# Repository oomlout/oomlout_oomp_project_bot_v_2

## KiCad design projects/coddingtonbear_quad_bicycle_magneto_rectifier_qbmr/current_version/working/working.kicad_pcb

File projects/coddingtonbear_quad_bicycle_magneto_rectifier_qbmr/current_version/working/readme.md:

# quad_bicycle_magneto_rectifier
 
## summary 
* id: coddingtonbear_quad_bicycle_magneto_rectifier_qbmr
* user: coddingtonbear
* name: quad_bicycle_magneto_rectifier
* board: qbmr
* repo: https://github.com/coddingtonbear/quad-bicycle-magneto-rectifier
* src_file_repo_kicad_pcb: hardware/qbmr.kicad_pcb
* src_file_repo_kicad_pcb_link: https://github.com/coddingtonbear/quad-bicycle-magneto-rectifier/tree/master/hardware/qbmr.kicad_pcb

* src_file_repo_sch: hardware/qbmr.sch
* src_file_repo_sch_link: https://github.com/coddingtonbear/quad-bicycle-magneto-rectifier/tree/master/hardware/qbmr.sch
* full details link: https://github.com/oomlout/oomlout_oomp_project_bot_v_2/tree/main/projects/coddingtonbear_quad_bicycle_magneto_rectifier_qbmr/current_version/working

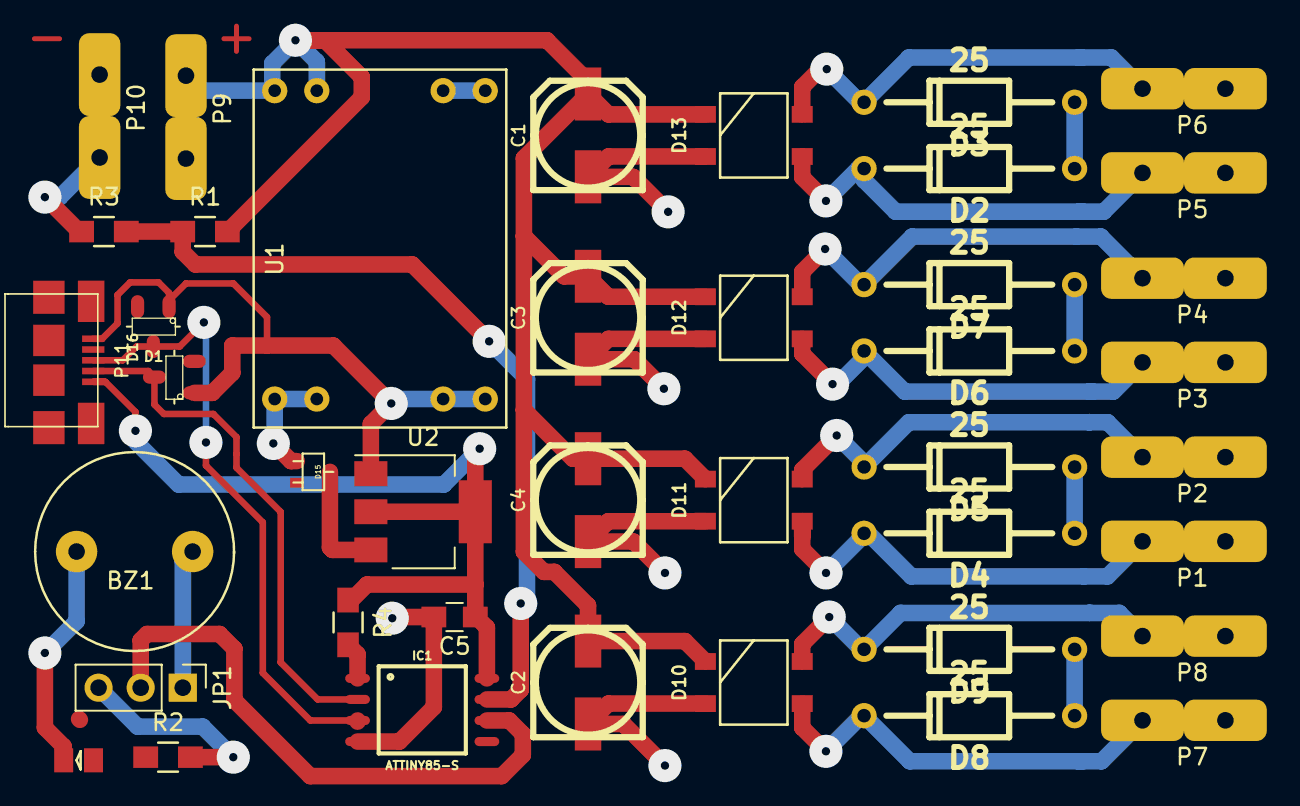
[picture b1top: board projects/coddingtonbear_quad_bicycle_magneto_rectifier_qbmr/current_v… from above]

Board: 2 copper layers, 41 parts (0 on the bottom side), 25 nets.

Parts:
BZ1: Buzzer; 12mm_buzzer
C1, C2, C3, C4: ?; SMD_PANASONIC_D
C5: 0.1u; C_0805_HandSoldering
D1, D16: 3.6; DIODE-SOT-23-3
D2, D3, D4, D5, D6, D7, D8, D9: 25; DO204AL_500
D10, D11, D12, D13: MB24S(+); SM-TO-269AA
D14: LED; 0805-LED
D15: D; SOT323_diode
IC1: ATTINY85-S; SOIC8
JP1: Jumper_NC_Dual; Pin_Header_Straight_1x03_Pitch2.54mm
P1, P2, P3, P4, P5, P6, P7, P8: CONN_01X01; TAB
P9: VCC; TAB
P10: GND; TAB
P11: USB_OTG; MICRO-B_USB-INVERTED
R1: 1k; R_0805_HandSoldering
R2: 500; R_0805_HandSoldering
R3: 200; R_0805_HandSoldering
R4: 10k; R_0805_HandSoldering
U1: MP1584EN
U2: AP111750; SOT-223

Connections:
GND: BZ1.2, C1.2, C2.2, C3.2, C4.2, C5.2, D1.2, D10.2, D11.2, D12.2, D13.2, D14.1, D16.2, IC1.4, P10.1, P11.5, R3.1, U1.1, U1.3, U2.1
unnamed: BZ1.1, JP1.1
unnamed: D2.2, D3.2
unnamed: D4.2, D5.2
unnamed: D6.2, D7.2
unnamed: D8.2, D9.2
unnamed: D8.1, D10.3, P7.1
unnamed: D9.1, D10.4, P8.1
unnamed: D4.1, D11.3, P1.1
unnamed: D5.1, D11.4, P2.1
unnamed: D6.1, D12.3, P3.1
unnamed: D7.1, D12.4, P4.1
unnamed: D2.1, D13.3, P5.1
unnamed: D3.1, D13.4, P6.1
unnamed: D14.2, R2.1
unnamed: D15.1, U2.3
unnamed: D15.2, U1.4
unnamed: IC1.1, R4.2
unnamed: IC1.6, JP1.2
unnamed: IC1.7, R1.1, R3.2
unnamed: JP1.3, R2.2
USBD+: D16.1, IC1.3, P11.3
USBD-: D1.1, IC1.2, P11.2
VCC: C1.1, C2.1, C3.1, C4.1, D10.1, D11.1, D12.1, D13.1, P9.1, R1.2, U1.2
VUSB: C5.1, IC1.8, P11.1, R4.1, U2.2, U2.4

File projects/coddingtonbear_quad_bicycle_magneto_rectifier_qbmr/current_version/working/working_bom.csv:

"Id";"Designator";"Footprint";"Quantity";"Designation";"Supplier and ref";
1;"P10";"TAB";1;"GND";;;
2;"P9";"TAB";1;"VCC";;;
3;"P8,P7,P6,P5,P4,P1,P2,P3";"TAB";8;"CONN_01X01";;;
4;"D12,D10,D11,D13";"SM-TO-269AA";4;"MB24S(+)";;;
5;"C4,C3,C2,C1";"SMD_PANASONIC_D";4;"?";;;
6;"R1";"R_0805_HandSoldering";1;"1k";;;
7;"R2";"R_0805_HandSoldering";1;"500";;;
8;"D14";"0805-LED";1;"LED";;;
9;"BZ1";"12mm_buzzer";1;"Buzzer";;;
10;"D15";"SOT323_diode";1;"D";;;
11;"U1";"MP1584EN";1;"MP1584EN";;;
12;"P11";"MICRO-B_USB-INVERTED";1;"USB_OTG";;;
13;"IC1";"SOIC8";1;"ATTINY85-S";;;
14;"R3";"R_0805_HandSoldering";1;"200";;;
15;"U2";"SOT-223";1;"AP111750";;;
16;"C5";"C_0805_HandSoldering";1;"0.1u";;;
17;"D1,D16";"DIODE-SOT-23-3";2;"3.6";;;
18;"JP1";"Pin_Header_Straight_1x03_Pitch2.54mm";1;"Jumper_NC_Dual";;;
19;"D2,D3,D4,D5,D6,D7,D8,D9";"DO204AL_500";8;"25";;;
20;"R4";"R_0805_HandSoldering";1;"10k";;;

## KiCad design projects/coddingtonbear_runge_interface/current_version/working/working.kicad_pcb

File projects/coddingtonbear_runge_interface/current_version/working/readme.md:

# runge
 
## summary 
* id: coddingtonbear_runge_interface
* user: coddingtonbear
* name: runge
* board: interface
* repo: https://github.com/coddingtonbear/runge
* src_file_repo_kicad_pcb: hardware/interface/interface.kicad_pcb
* src_file_repo_kicad_pcb_link: https://github.com/coddingtonbear/runge/tree/master/hardware/interface/interface.kicad_pcb

* src_file_repo_sch: hardware/interface/interface.sch
* src_file_repo_sch_link: https://github.com/coddingtonbear/runge/tree/master/hardware/interface/interface.sch
* full details link: https://github.com/oomlout/oomlout_oomp_project_bot_v_2/tree/main/projects/coddingtonbear_runge_interface/current_version/working

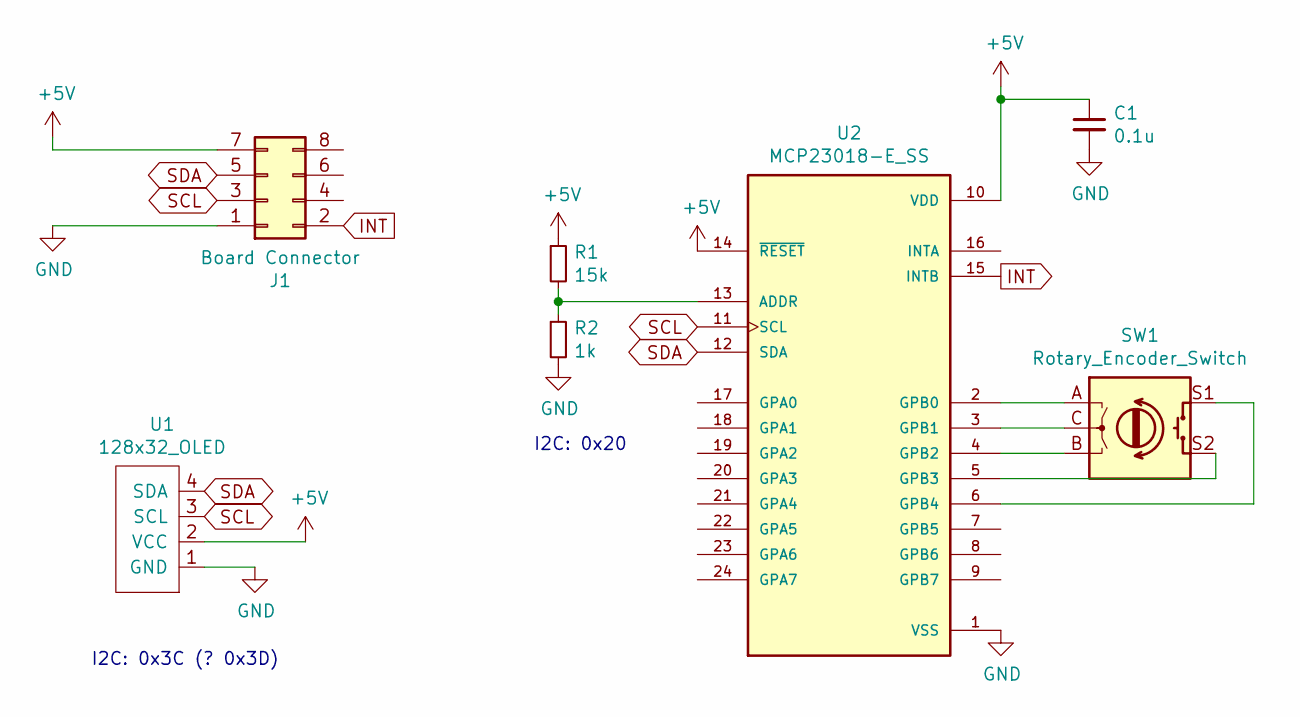
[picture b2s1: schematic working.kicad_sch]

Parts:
C1: 0.1u; 0805_Milling
J1: Board Connector; IDC-Header_2x04_P2.54mm_Vertical
R1: 15k; 0805_Milling
R2: 1k; 0805_Milling
SW1: Rotary_Encoder_Switch; RotaryEncoder_Alps_EC12E-Switch_Vertical_H20mm
U1: 128x32_OLED
U2: MCP23018-E_SS; SSOP-24_5.3x8.2mm_P0.65mm; PARTREV N/A

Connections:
+5V: C1.1, J1.7, R1.1, U1.2 (VCC), U2.10 (VDD), U2.14 (~RESET)
GND: C1.2, J1.1, R2.2, U1.1 (GND), U2.1 (VSS)
INT: J1.2, U2.15 (INTB)
unnamed: R1.2, R2.1, U2.13 (ADDR)
unnamed: SW1.A, U2.2 (GPB0)
unnamed: SW1.B, U2.4 (GPB2)
unnamed: SW1.C, U2.3 (GPB1)
unnamed: SW1.S1, U2.6 (GPB4)
unnamed: SW1.S2, U2.5 (GPB3)
SCL: J1.3, U1.3 (SCL), U2.11 (SCL)
SDA: J1.5, U1.4 (SDA), U2.12 (SDA)

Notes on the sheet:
I2C: 0x20
I2C: 0x3C (? 0x3D)

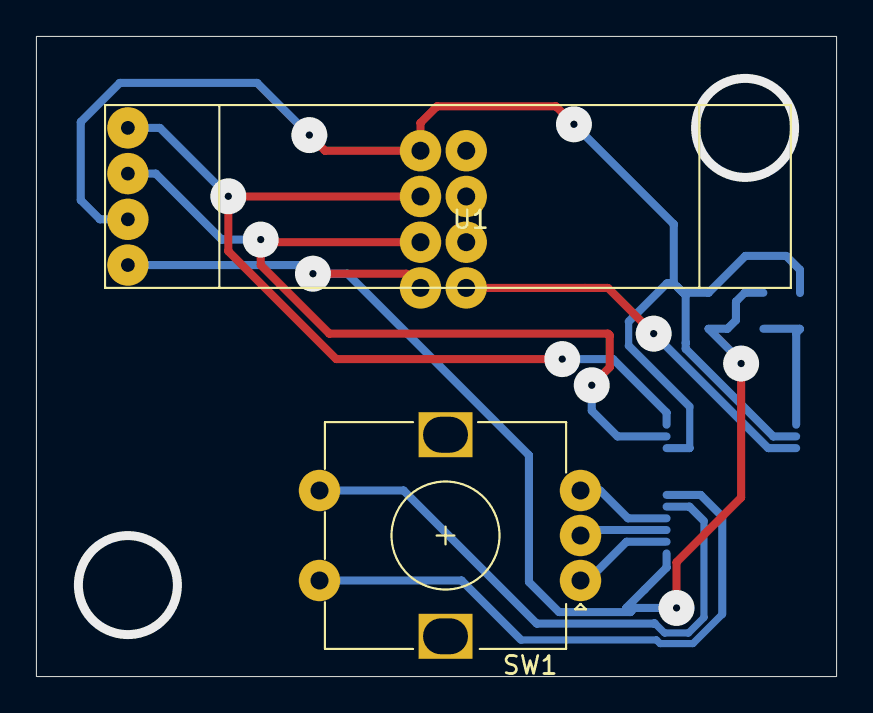
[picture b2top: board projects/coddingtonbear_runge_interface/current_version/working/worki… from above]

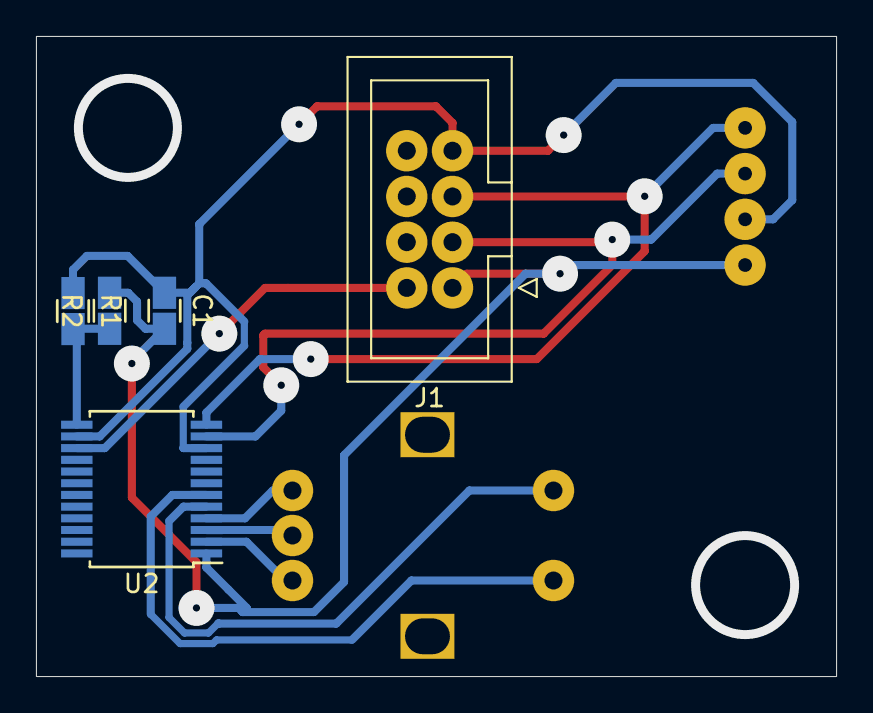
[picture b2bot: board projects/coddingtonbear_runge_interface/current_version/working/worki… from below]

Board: 2 copper layers, 44.4 x 35.6 mm, 7 parts (5 on the bottom side), 11 nets.

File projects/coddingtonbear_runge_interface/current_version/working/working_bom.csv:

"Id";"Designator";"Footprint";"Quantity";"Designation";"Supplier and ref";
1;"U1";"128x32_OLED";1;"128x32_OLED";;;
2;"SW1";"RotaryEncoder_Alps_EC12E-Switch_Vertical_H20mm";1;"Rotary_Encoder_Switch";;;
3;"C1";"0805_Milling";1;"0.1u";;;
4;"R1";"0805_Milling";1;"15k";;;
5;"R2";"0805_Milling";1;"1k";;;
6;"U2";"SSOP-24_5.3x8.2mm_P0.65mm";1;"MCP23018-E_SS";;;
7;"J1";"IDC-Header_2x04_P2.54mm_Vertical";1;"Board Connector";;;

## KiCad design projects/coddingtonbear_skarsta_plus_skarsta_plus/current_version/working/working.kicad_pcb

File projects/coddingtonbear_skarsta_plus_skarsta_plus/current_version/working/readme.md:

# skarsta_plus
 
## summary 
* id: coddingtonbear_skarsta_plus_skarsta_plus
* user: coddingtonbear
* name: skarsta_plus
* board: skarsta_plus
* repo: https://github.com/coddingtonbear/skarsta-plus
* src_file_repo_kicad_pcb: hardware/skarsta_plus.kicad_pcb
* src_file_repo_kicad_pcb_link: https://github.com/coddingtonbear/skarsta-plus/tree/master/hardware/skarsta_plus.kicad_pcb

* src_file_repo_sch: hardware/skarsta_plus.sch
* src_file_repo_sch_link: https://github.com/coddingtonbear/skarsta-plus/tree/master/hardware/skarsta_plus.sch
* full details link: https://github.com/oomlout/oomlout_oomp_project_bot_v_2/tree/main/projects/coddingtonbear_skarsta_plus_skarsta_plus/current_version/working

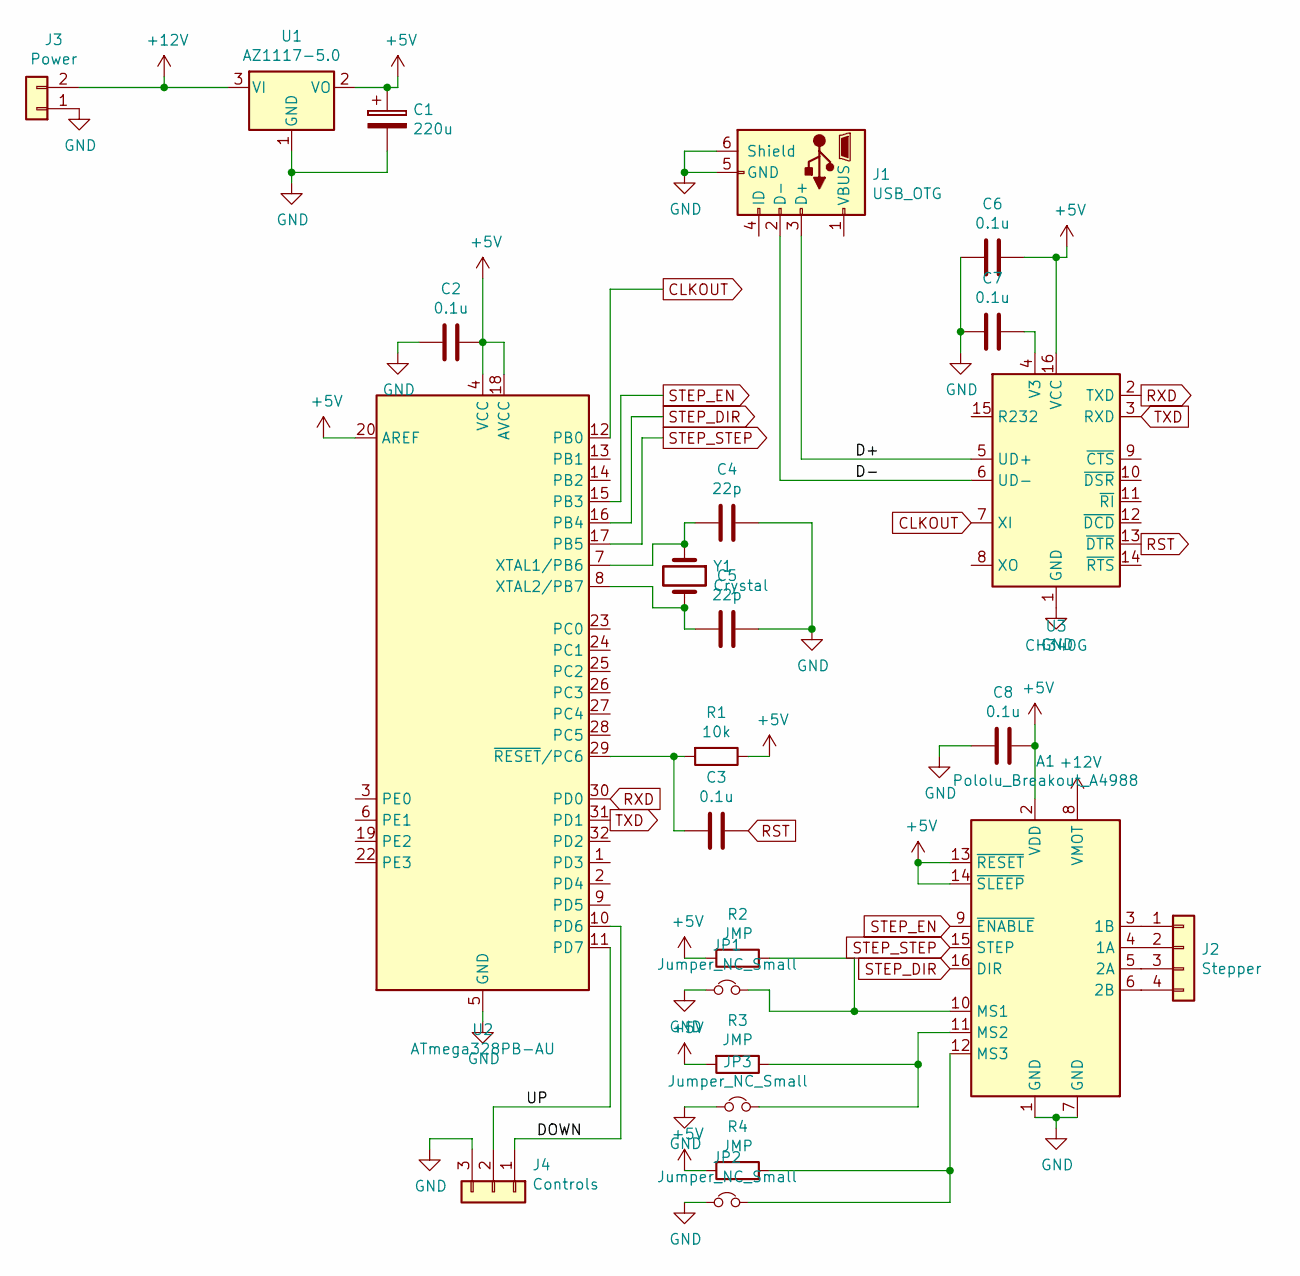
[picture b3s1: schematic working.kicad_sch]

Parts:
A1: Pololu_Breakout_A4988; Pololu_Stepper_Breakout
C1: 220u; CP_Elec_10x10.5
C2, C3, C6, C7, C8: 0.1u; 0805_Milling
C4, C5: 22p; 0805_Milling
J1: USB_OTG; UJ2-MIBH-4-SMT
J2: Stepper; JST_XH_B04B-XH-A_04x2.50mm_Straight_LargePads
J3: Power; JST_XH_B02B-XH-A_02x2.50mm_Straight_LargePads
J4: Controls; JST_XH_B03B-XH-A_03x2.50mm_Straight_LargePads
JP1, JP2, JP3: Jumper_NC_Small; SolderJumper-2_P1.3mm_Bridged_RoundedPad1.0x1.5mm
R1: 10k; 0805_Milling
R2, R3, R4: JMP; SolderJumper-2_P1.3mm_Open_RoundedPad1.0x1.5mm
U1: AZ1117-5.0; SOT-223-3_TabPin2
U2: ATmega328PB-AU; TQFP-32_7x7mm_P0.8mm
U3: CH340G; SOIC-16_3.9x9.9mm_P1.27mm
Y1: Crystal; Crystal_HC49-U_Vertical

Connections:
+5V: A1.2 (VDD), A1.13 (~RESET), A1.14 (~SLEEP), C1.1, C2.1, C6.1, C8.1, R1.1, R2.2, R3.2, R4.2, U1.2 (VO), U2.4 (VCC), U2.18 (AVCC), U2.20 (AREF), U3.16 (VCC)
+12V: A1.8 (VMOT), J3.2, U1.3 (VI)
/D+: J1.3 (D+), U3.5 (UD+)
/D-: J1.2 (D-), U3.6 (UD-)
/DOWN: J4.1, U2.10 (PD6)
/UP: J4.2, U2.11 (PD7)
CLKOUT: U2.12 (PB0), U3.7 (XI)
GND: A1.1 (GND), A1.7 (GND), C1.2, C2.2, C4.1, C5.1, C6.2, C7.2, C8.2, J1.5 (GND), J1.6 (Shield), J3.1, J4.3, JP1.1, JP2.1, JP3.1, U1.1 (GND), U2.5 (GND), U2.21 (GND), U3.1 (GND)
unnamed: A1.3 (1B), J2.1
unnamed: A1.4 (1A), J2.2
unnamed: A1.5 (2A), J2.3
unnamed: A1.6 (2B), J2.4
unnamed: A1.10 (MS1), JP1.2, R2.1
unnamed: A1.11 (MS2), JP3.2, R3.1
unnamed: A1.12 (MS3), JP2.2, R4.1
unnamed: C3.2, R1.2, U2.29 (~RESET/PC6)
unnamed: C4.2, U2.7 (XTAL1/PB6), Y1.1
unnamed: C5.2, U2.8 (XTAL2/PB7), Y1.2
unnamed: C7.1, U3.4 (V3)
RST: C3.1, U3.13 (~DTR)
RXD: U2.30 (PD0), U3.2 (TXD)
STEP_DIR: A1.16 (DIR), U2.16 (PB4)
STEP_EN: A1.9 (~ENABLE), U2.15 (PB3)
STEP_STEP: A1.15 (STEP), U2.17 (PB5)
TXD: U2.31 (PD1), U3.3 (RXD)

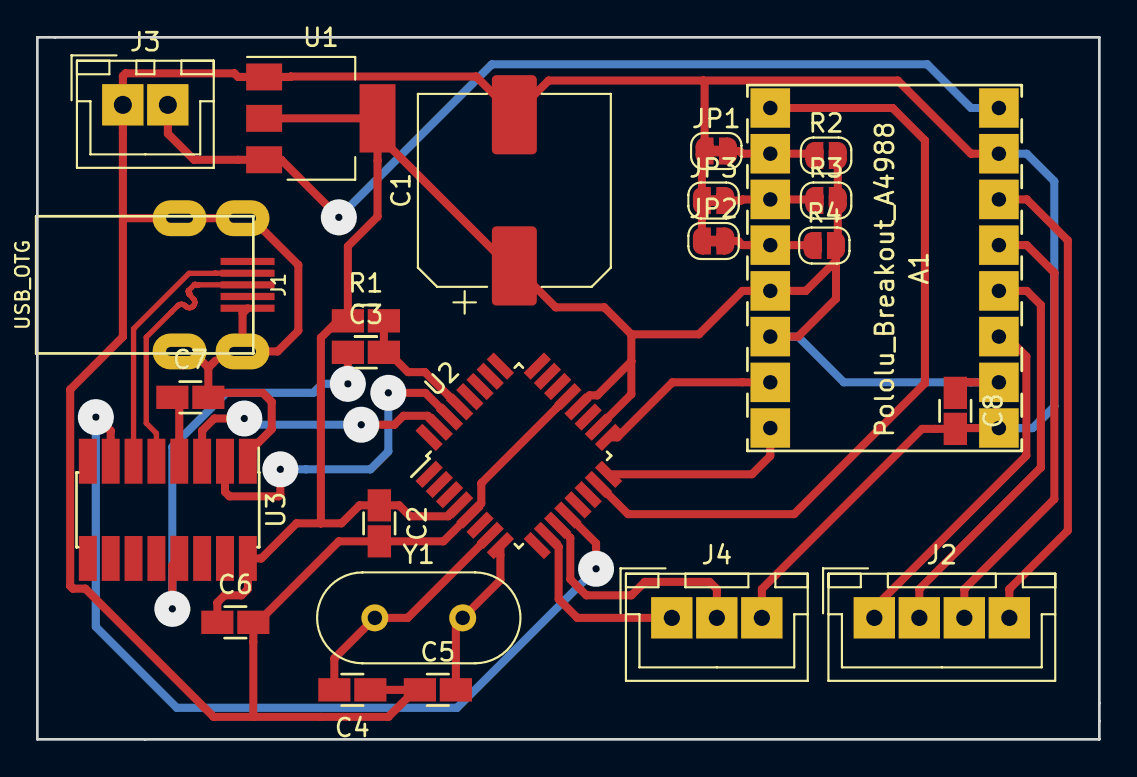
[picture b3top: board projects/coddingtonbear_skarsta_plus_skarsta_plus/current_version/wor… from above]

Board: 2 copper layers, 59.0 x 39.0 mm, 24 parts (0 on the bottom side), 25 nets.

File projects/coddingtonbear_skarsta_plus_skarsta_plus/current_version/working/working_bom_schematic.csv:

"Source:","C:\gh\oomlout_oomp_project_bot_v_2\projects\coddingtonbear_skarsta_plus_skarsta_plus\current_version\working\working.kicad_sch"
"Date:","28/09/2023 23:45:36"
"Tool:","Eeschema 7.0.6"
"Generator:","C:/Program Files/KiCad/7.0/bin/scripting/plugins/bom_csv_grouped_by_value_with_fp.py"
"Component Count:","24"
"Ref","Qnty","Value","Cmp name","Footprint","Description","Vendor","DNP"
"A1","1","Pololu_Breakout_A4988","Pololu_Breakout_A4988","coddingtonbear:Pololu_Stepper_Breakout","Pololu Breakout Board, Stepper Driver A4988","",""
"C1","1","220u","CP-Device","Capacitor_SMD:CP_Elec_10x10.5","","",""
"C2, C3, C6, C7, C8","5","0.1u","C","coddingtonbear:0805_Milling","Unpolarized capacitor","",""
"C4, C5","2","22p","C","coddingtonbear:0805_Milling","Unpolarized capacitor","",""
"J1","1","USB_OTG","USB_OTG-Connector","coddingtonbear:UJ2-MIBH-4-SMT","","",""
"J2","1","Stepper","Conn_01x04","coddingtonbear:JST_XH_B04B-XH-A_04x2.50mm_Straight_LargePads","Generic connector, single row, 01x04, script generated (kicad-library-utils/schlib/autogen/connector/)","",""
"J3","1","Power","Conn_01x02","coddingtonbear:JST_XH_B02B-XH-A_02x2.50mm_Straight_LargePads","Generic connector, single row, 01x02, script generated (kicad-library-utils/schlib/autogen/connector/)","",""
"J4","1","Controls","Conn_01x03","coddingtonbear:JST_XH_B03B-XH-A_03x2.50mm_Straight_LargePads","Generic connector, single row, 01x03, script generated (kicad-library-utils/schlib/autogen/connector/)","",""
"JP1, JP2, JP3","3","Jumper_NC_Small","Jumper_NC_Small-Device","Jumper:SolderJumper-2_P1.3mm_Bridged_RoundedPad1.0x1.5mm","","",""
"R1","1","10k","R","coddingtonbear:0805_Milling","Resistor","",""
"R2, R3, R4","3","JMP","R","Jumper:SolderJumper-2_P1.3mm_Open_RoundedPad1.0x1.5mm","Resistor","",""
"U1","1","AZ1117-5.0","AZ1117-5.0","Package_TO_SOT_SMD:SOT-223-3_TabPin2","1A 20V Fixed LDO Linear Regulator, 5.0V, SOT-89/SOT-223/TO-220/TO-252/TO-263","",""
"U2","1","ATmega328PB-AU","ATmega328PB-AU-MCU_Microchip_ATmega","Package_QFP:TQFP-32_7x7mm_P0.8mm","","",""
"U3","1","CH340G","CH340G","Package_SO:SOIC-16_3.9x9.9mm_P1.27mm","USB serial converter, UART, SOIC-16","",""
"Y1","1","Crystal","Crystal","Crystal:Crystal_HC49-U_Vertical","Two pin crystal","",""

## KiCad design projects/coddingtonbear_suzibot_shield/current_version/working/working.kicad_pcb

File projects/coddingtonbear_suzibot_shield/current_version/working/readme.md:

# suzibot
 
## summary 
* id: coddingtonbear_suzibot_shield
* user: coddingtonbear
* name: suzibot
* board: shield
* repo: https://github.com/coddingtonbear/suzibot
* src_file_repo_kicad_pcb: hardware/shield/shield.kicad_pcb
* src_file_repo_kicad_pcb_link: https://github.com/coddingtonbear/suzibot/tree/master/hardware/shield/shield.kicad_pcb

* src_file_repo_sch: hardware/shield/shield.sch
* src_file_repo_sch_link: https://github.com/coddingtonbear/suzibot/tree/master/hardware/shield/shield.sch
* full details link: https://github.com/oomlout/oomlout_oomp_project_bot_v_2/tree/main/projects/coddingtonbear_suzibot_shield/current_version/working

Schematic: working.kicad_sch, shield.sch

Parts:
C1, C2: 22p; C_0805_HandSoldering
C3: 0.01u; C_0805_HandSoldering
C4: 22u; C_Radial_D5_L6_P2.5
C5, C6, C7, C8: 0.1u; C_0805_HandSoldering
D1: ORANGE; LED_0805
D2: RED; LED_0805
D3: BLUE; LED_0805
E1: JNHUAMAO_HM-10; JNHUAMAO_26.9X13X2.2_BOARD
J10: USB_OTG; USB_Mini-B
JP1, JP2: Pin_Header_Straight_1x03
PA0, PA1: DP_DEVICES.V6_M1X8
PB0, PB1: DP_DEVICES.V6_M1X8
PC0, PC1: DP_DEVICES.V6_M1X8
PD0, PD1: DP_DEVICES.V6_M1X8
PROG0, PROG1: DP_DEVICES.V6_M1X6
PWR0, PWR1, PWR2, PWR3: DP_DEVICES.V6_M1X3
R1: 68; R_0805_HandSoldering
R2: 150; R_0805_HandSoldering
R3: 100; R_0805_HandSoldering
R4: DTR-RST; C_0805
R5: RTS-RST; C_0805
R6: 3V3USB; C_0805
SW1: RESET; NANO-SWITCH
U1: LM1117; SPARKFUN-POWERIC_SOT223
U2: 74LV4052; SOIC-16_3.9x9.9mm_Pitch1.27mm
U3: TXB0104; SOIC-14_3.9x8.7mm_Pitch1.27mm
U$1: CH340G_SOIC16
Y1: 12M; Crystal_HC49-U_Vertical

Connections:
/3V3: C7.1, E1.11 (RESET), E1.12 (+3.3V), JP1.1, JP2.1, R6.2, U1.2 (OUT), U1.4 (OUT), U3.1 (VA), U3.8 (OE)
/CONN-BT: E1.24 (LED), U3.5 (A4)
/D-: J10.2 (D-), U$1.6 (D-)
/DTR: PROG0.1, PROG1.1, R4.2, R5.2, SW1.1, U3.11 (B3)
/DTR-BT: E1.25 (PIO2), U3.4 (A3)
/DTR-USB: R4.1, U$1.13 (DTR)
/N$2: JP1.3, JP2.3, PWR0.2, PWR1.2, R1.1
/N$6: J10.1 (VBUS), PROG0.4, PROG1.4
/N$8: C3.2, R6.1, U$1.4 (V3)
/N$9: PD0.8, PD1.8
/N$10: PD0.7, PD1.7
/N$11: PD0.6, PD1.6
/N$12: PD0.5, PD1.5
/N$13: PD0.4, PD1.4
/N$14: PD0.3, PD1.3
/N$15: PD0.2, PD1.2
/N$16: PD0.1, PD1.1
/N$17: PC0.8, PC1.8
/N$18: PC0.7, PC1.7
/N$19: PC0.6, PC1.6
/N$20: PROG0.5, PROG1.5
/N$21: PC0.4, PC1.4, R3.2, U2.10 (A0), U3.10 (B4)
/N$22: PC0.3, PC1.3
/N$23: PC0.2, PC1.2
/N$24: PC0.1, PC1.1
/N$25: PB0.8, PB1.8
/N$26: PB0.7, PB1.7
/N$27: PB0.6, PB1.6
/N$28: PB0.5, PB1.5
/N$29: PB0.4, PB1.4
/N$30: PB0.3, PB1.3
/N$31: PB0.2, PB1.2
/N$32: PB0.1, PB1.1
/N$33: PA0.8, PA1.8
/N$34: PA0.7, PA1.7
/N$35: PA0.6, PA1.6
/N$36: PA0.5, PA1.5
/N$37: PA0.4, PA1.4
/N$38: PA0.3, PA1.3
/N$39: PA0.2, PA1.2
/N$40: PA0.1, PA1.1
/N$44: JP1.2, PWR3.2
/PB: PC0.5, PC1.5
/RX: PROG0.2, PROG1.2, U2.13 (X)
/RXD-CH340G: U2.12 (X0), U$1.3 (RX)
/TX: PROG0.3, PROG1.3, U2.3 (Y)
/XO: C2.1, U$1.8 (XO), Y1.1
unnamed: D1.2 (A), R1.2
unnamed: D2.2 (A), R2.2
unnamed: D3.2 (A), R3.1
unnamed: E1.1 (UART_TX), U3.2 (A1)
unnamed: E1.2 (UART_RX), U3.3 (A2)
unnamed: R5.1, U$1.14 (RTS)
unnamed: U2.5 (Y1), U3.13 (B1)
unnamed: U2.14 (X1), U3.12 (B2)

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
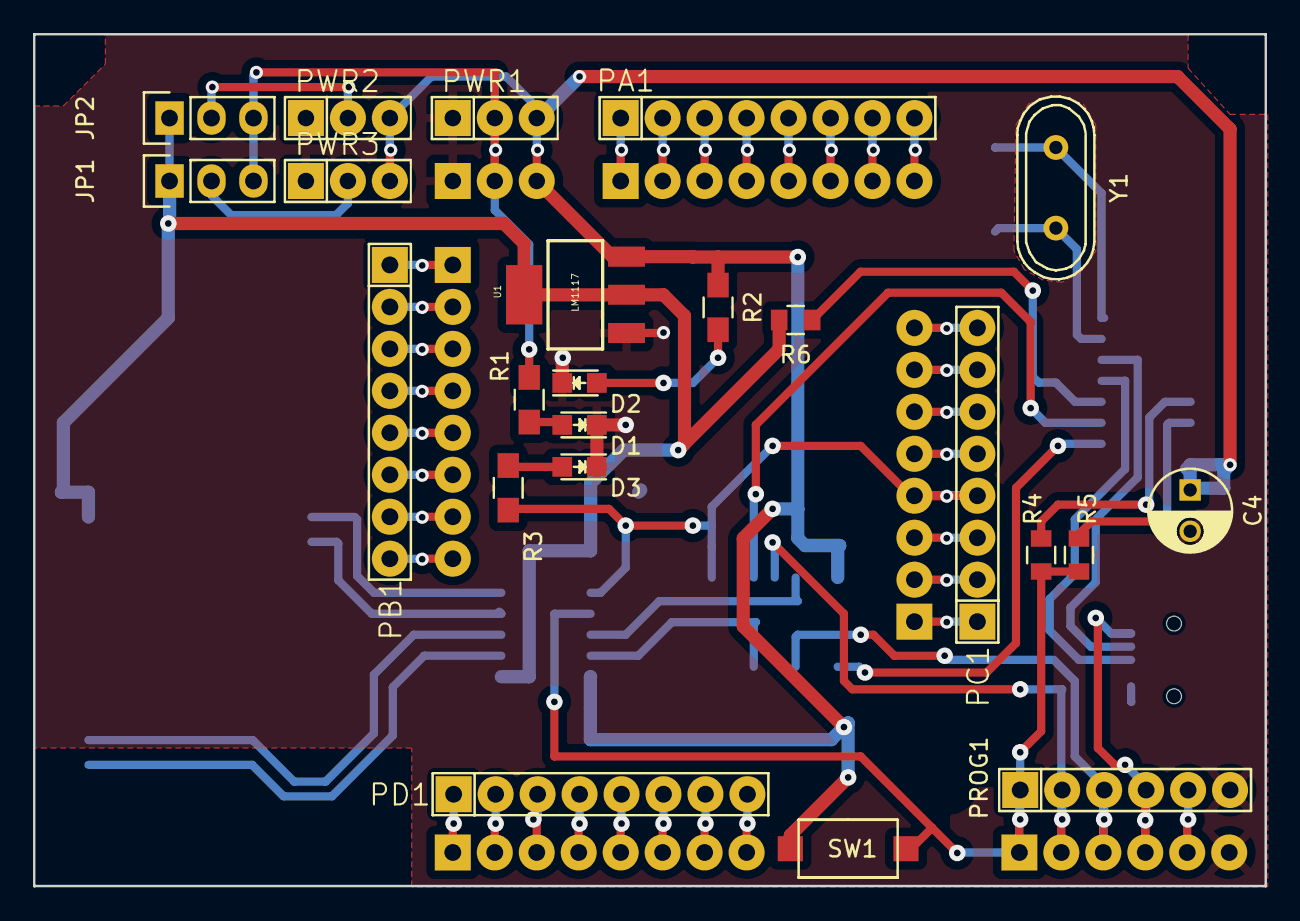
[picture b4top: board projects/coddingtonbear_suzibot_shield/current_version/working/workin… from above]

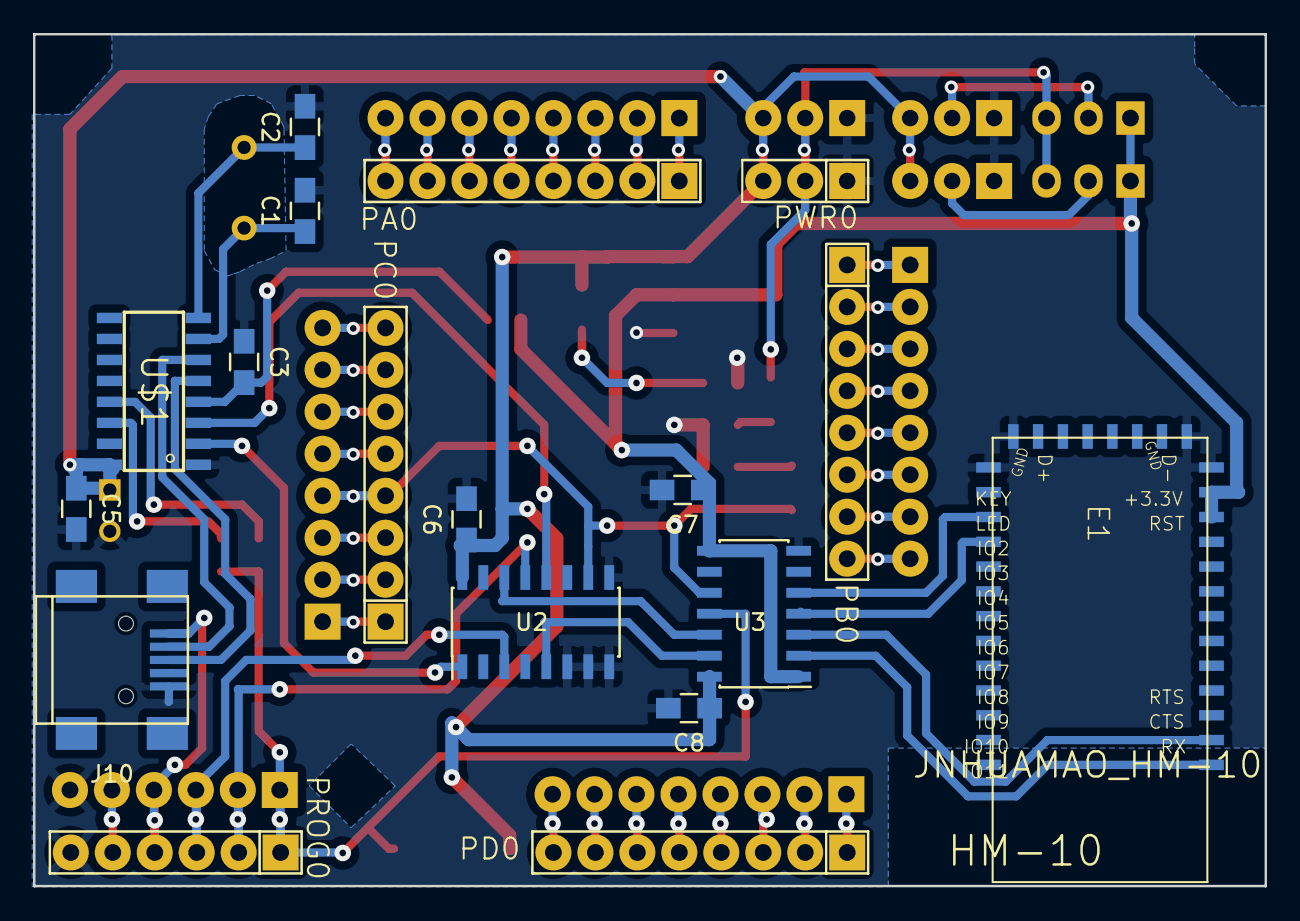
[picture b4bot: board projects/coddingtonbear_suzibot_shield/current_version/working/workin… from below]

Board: 2 copper layers, 74.5 x 51.6 mm, 41 parts (18 on the bottom side), 61 nets.

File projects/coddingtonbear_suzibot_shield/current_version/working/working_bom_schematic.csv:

"Source:","C:\gh\oomlout_oomp_project_bot_v_2\projects\coddingtonbear_suzibot_shield\current_version\working\working.kicad_sch"
"Date:","28/09/2023 23:53:30"
"Tool:","Eeschema 7.0.6"
"Generator:","C:/Program Files/KiCad/7.0/bin/scripting/plugins/bom_csv_grouped_by_value_with_fp.py"
"Component Count:","41"
"Ref","Qnty","Value","Cmp name","Footprint","Description","Vendor","DNP"
"C1, C2","2","22p","SPARKFUN-CAPACITORS_CAP","Capacitors_SMD:C_0805_HandSoldering","","",""
"C3","1","0.01u","SPARKFUN-CAPACITORS_CAP","Capacitors_SMD:C_0805_HandSoldering","","",""
"C4","1","22u","CP","Capacitors_THT:C_Radial_D5_L6_P2.5","","",""
"C5, C6, C7, C8","4","0.1u","C","Capacitors_SMD:C_0805_HandSoldering","","",""
"D1","1","ORANGE","LED","LEDs:LED_0805","","",""
"D2","1","RED","LED","LEDs:LED_0805","","",""
"D3","1","BLUE","LED","LEDs:LED_0805","","",""
"E1","1","JNHUAMAO_HM-10","JNHUAMAO_HM-10","shield:JNHUAMAO_26.9X13X2.2_BOARD","","",""
"J10","1","USB_OTG","USB_OTG","shield-pretty:USB_Mini-B","","",""
"JP1, JP2","2","~","SPARKFUN-RETIRED_JUMPER-3","Pin_Headers:Pin_Header_Straight_1x03","","",""
"PA0, PA1","2","~","DP_DEVICES.V6_CON_HEADER_1X08","shield:DP_DEVICES.V6_M1X8","","",""
"PB0, PB1","2","~","DP_DEVICES.V6_CON_HEADER_1X08","shield:DP_DEVICES.V6_M1X8","","",""
"PC0, PC1","2","~","DP_DEVICES.V6_CON_HEADER_1X08","shield:DP_DEVICES.V6_M1X8","","",""
"PD0, PD1","2","~","DP_DEVICES.V6_CON_HEADER_1X08","shield:DP_DEVICES.V6_M1X8","","",""
"PROG0, PROG1","2","~","DP_DEVICES.V6_CON_HEADER_1X06","shield:DP_DEVICES.V6_M1X6","","",""
"PWR0, PWR1, PWR2, PWR3","4","~","DP_DEVICES.V6_CON_HEADER_1X03","shield:DP_DEVICES.V6_M1X3","","",""
"R1","1","68","R","Resistors_SMD:R_0805_HandSoldering","","",""
"R2","1","150","R","Resistors_SMD:R_0805_HandSoldering","","",""
"R3","1","100","R","Resistors_SMD:R_0805_HandSoldering","","",""
"R4","1","DTR-RST","R","Capacitors_SMD:C_0805","","",""
"R5","1","RTS-RST","R","Capacitors_SMD:C_0805","","",""
"R6","1","3V3USB","R","Capacitors_SMD:C_0805","","",""
"SW1","1","RESET","SW_Push","shield-pretty:NANO-SWITCH","","",""
"U1","1","LM1117","SPARKFUN-POWERIC_V_REG_LM1117","shield:SPARKFUN-POWERIC_SOT223","","",""
"U2","1","74LV4052","4052","Housings_SOIC:SOIC-16_3.9x9.9mm_Pitch1.27mm","","",""
"U3","1","TXB0104","TXB0104","Housings_SOIC:SOIC-14_3.9x8.7mm_Pitch1.27mm","","",""
"U$1","1","~","CH340G_CH340G","shield:CH340G_SOIC16","","",""
"Y1","1","12M","Crystal","Crystals:Crystal_HC49-U_Vertical","","",""

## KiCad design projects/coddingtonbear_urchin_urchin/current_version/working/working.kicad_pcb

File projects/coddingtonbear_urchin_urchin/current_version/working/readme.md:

# urchin
 
## summary 
* id: coddingtonbear_urchin_urchin
* user: coddingtonbear
* name: urchin
* board: urchin
* repo: https://github.com/coddingtonbear/urchin
* src_file_repo_kicad_pcb: hardware/urchin.kicad_pcb
* src_file_repo_kicad_pcb_link: https://github.com/coddingtonbear/urchin/tree/master/hardware/urchin.kicad_pcb

* src_file_repo_sch: hardware/urchin.sch
* src_file_repo_sch_link: https://github.com/coddingtonbear/urchin/tree/master/hardware/urchin.sch
* full details link: https://github.com/oomlout/oomlout_oomp_project_bot_v_2/tree/main/projects/coddingtonbear_urchin_urchin/current_version/working

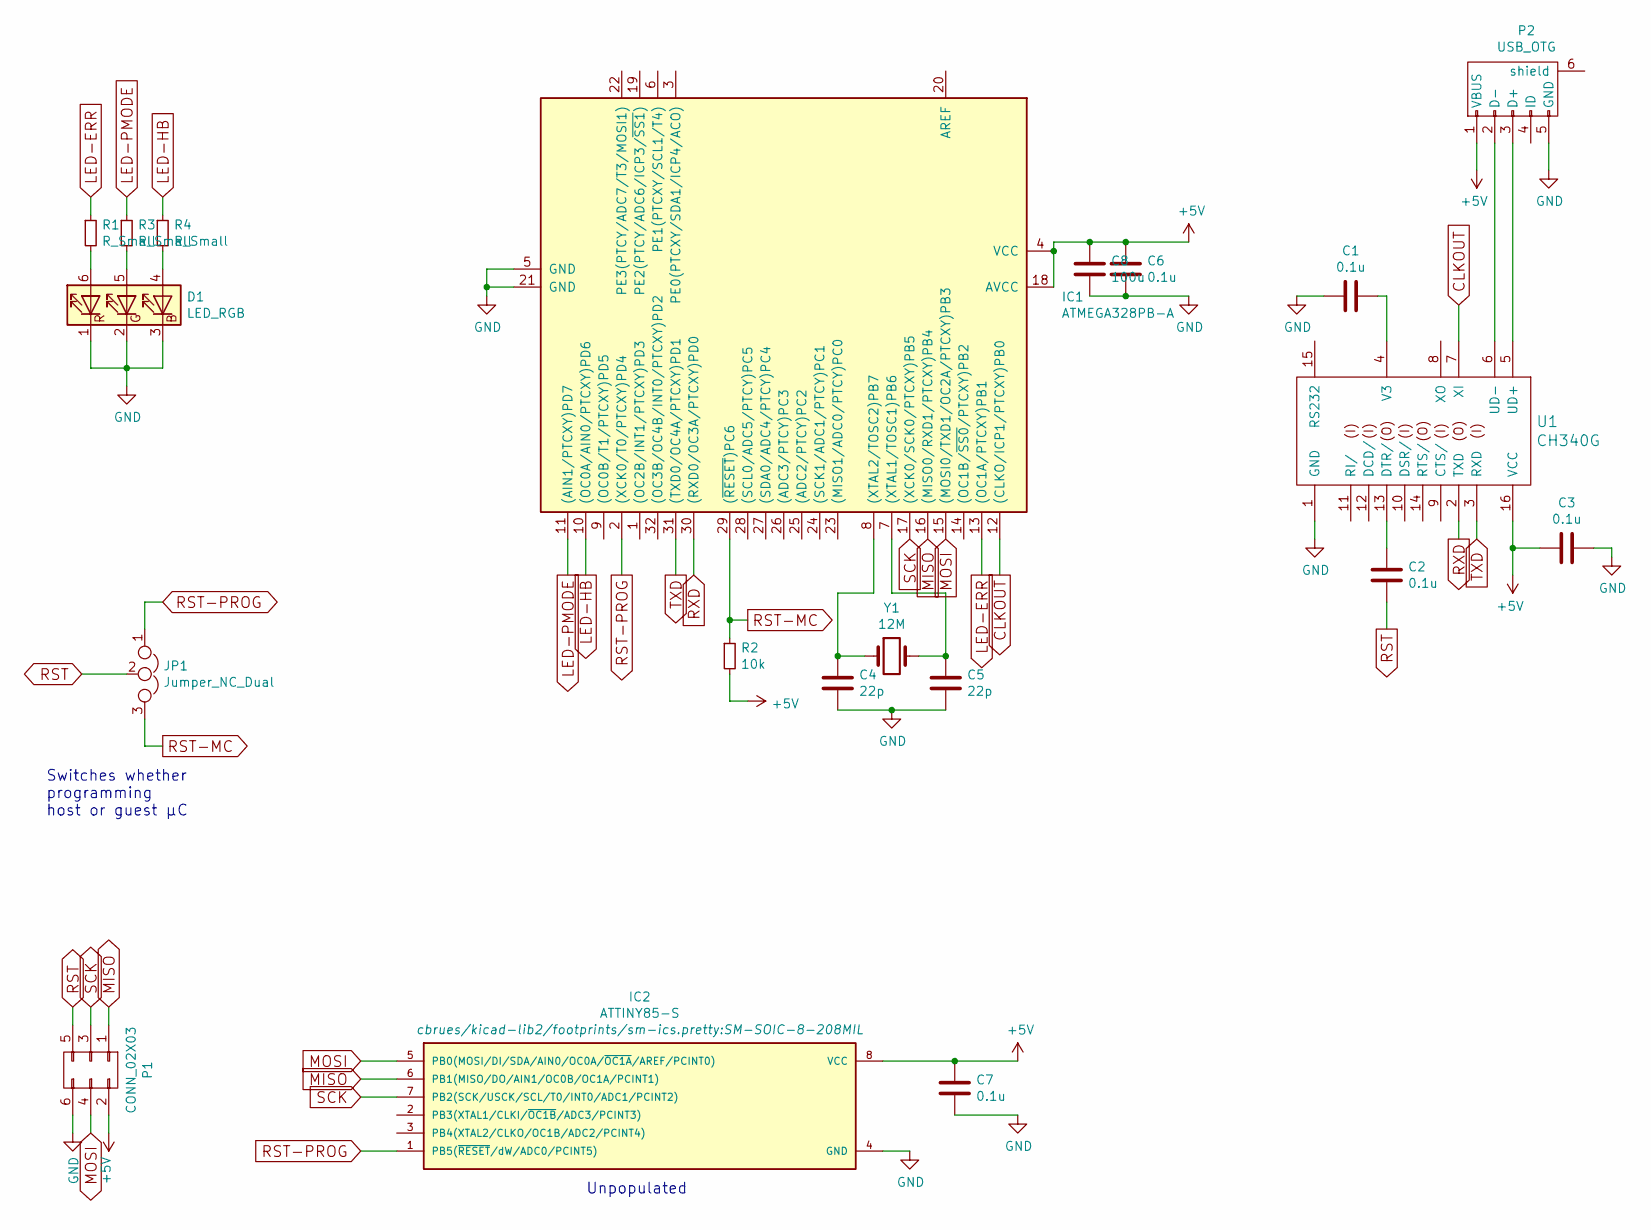
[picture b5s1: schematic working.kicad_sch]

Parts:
C1, C2, C3, C6, C7: 0.1u; C_0805_HandSoldering
C4, C5: 22p; C_0805_HandSoldering
C8: 100u; R_1206_HandSoldering
D1: LED_RGB; SLV6A-FKB
IC1: ATMEGA328PB-A; TQFP32_ATMEGA328P
IC2: ATTINY85-S; SM-SOIC-8-208MIL
JP1: Jumper_NC_Dual; Pin_Header_Straight_1x03_Pitch2.54mm_SMD_Pin1Left
P1: CONN_02X03; SMD_PIN_HEADER_02x03
P2: USB_OTG; MICRO-B_USB-INVERTED
R1, R3, R4: R_Small; R_0805_HandSoldering
R2: 10k; R_0805_HandSoldering
U1: CH340G; SOIC-16_3.9x9.9mm_Pitch1.27mm
Y1: 12M; Crystal_SMD_HC49-SD

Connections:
+5V: C3.1, C6.1, C7.1, C8.1, IC1.4 (VCC), IC1.18 (AVCC), IC2.8 (VCC), P1.2, P2.1 (VBUS), R2.2, U1.16 (VCC)
CLKOUT: IC1.12 ((CLKO/ICP1/PTCXY)PB0), U1.7 (XI)
GND: C1.1, C3.2, C4.2, C5.2, C6.2, C7.2, C8.2, D1.1 (RK), D1.2 (GK), D1.3 (BK), IC1.5 (GND), IC1.21 (GND), IC2.4 (GND), P1.6, P2.5 (GND), U1.1 (GND)
LED-ERR: IC1.13 ((OC1A/PTCXY)PB1), R1.1
LED-HB: IC1.10 ((OC0A/AIN0/PTCXY)PD6), R4.1
LED-PMODE: IC1.11 ((AIN1/PTCXY)PD7), R3.1
MISO: IC1.16 ((MISO0/RXD1/PTCXY)PB4), IC2.6 (PB1(MISO/DO/AIN1/OC0B/OC1A/PCINT1)), P1.1
MOSI: IC1.15 ((MOSI0/TXD1/OC2A/PTCXY)PB3), IC2.5 (PB0(MOSI/DI/SDA/AIN0/OC0A/~OC1A/AREF/PC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), P1.4
unnamed: C1.2, U1.4 (V3)
unnamed: C2.1, U1.13 (DTR/)
unnamed: C4.1, IC1.8 ((XTAL2/TOSC2)PB7), Y1.1
unnamed: C5.1, IC1.7 ((XTAL1/TOSC1)PB6), Y1.2
unnamed: D1.4 (BA), R4.2
unnamed: D1.5 (GA), R3.2
unnamed: D1.6 (RA), R1.2
unnamed: P2.2 (D-), U1.6 (UD-)
unnamed: P2.3 (D+), U1.5 (UD+)
RST: C2.2, JP1.2, P1.5
RST-MC: IC1.29 ((~RESET)PC6), JP1.3, R2.1
RST-PROG: IC1.2 ((XCK0/T0/PTCXY)PD4), IC2.1 (PB5(~RESET/dW/ADC0/PCINT5)), JP1.1
RXD: IC1.30 ((RXD0/OC3A/PTCXY)PD0), U1.2 (TXD)
SCK: IC1.17 ((XCK0/SCK0/PTCXY)PB5), IC2.7 (PB2(SCK/USCK/SCL/T0/INT0/ADC1/PCINT2)), P1.3
TXD: IC1.31 ((TXD0/OC4A/PTCXY)PD1), U1.3 (RXD)

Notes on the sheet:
Switches whether programming host or guest µC
Unpopulated

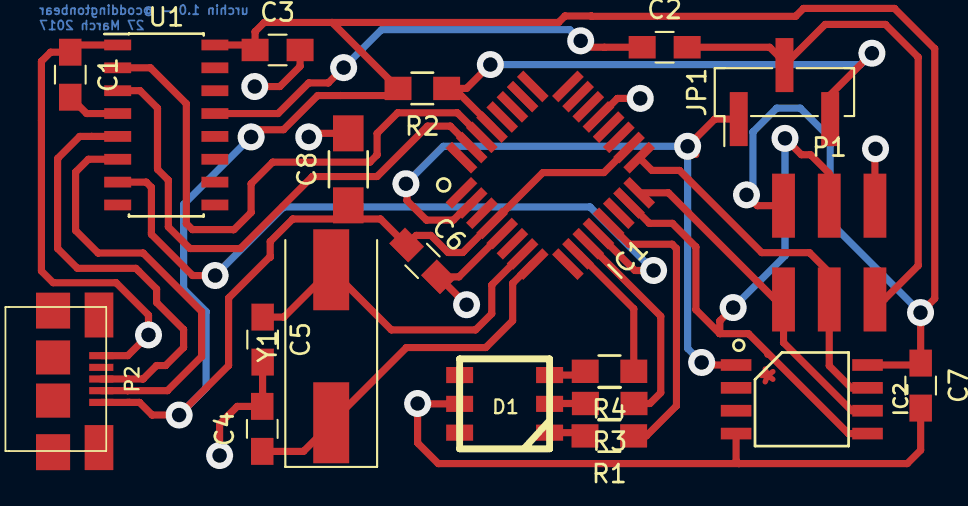
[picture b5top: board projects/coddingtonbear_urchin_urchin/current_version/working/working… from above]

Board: 2 copper layers, 20 parts (0 on the bottom side), 23 nets.

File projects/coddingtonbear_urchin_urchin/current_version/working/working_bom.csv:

"Id";"Designator";"Footprint";"Quantity";"Designation";"Supplier and ref";
1;"P2";"MICRO-B_USB-INVERTED";1;"USB_OTG";;;
2;"IC2";"SM-SOIC-8-208MIL";1;"ATTINY85-S";;;
3;"R4,R1,R3";"R_0805_HandSoldering";3;"R_Small";;;
4;"JP1";"Pin_Header_Straight_1x03_Pitch2.54mm_SMD_Pin1Left";1;"Jumper_NC_Dual";;;
5;"P1";"SMD_PIN_HEADER_02x03";1;"CONN_02X03";;;
6;"IC1";"TQFP32_ATMEGA328P";1;"ATMEGA328PB-A";;;
7;"R2";"R_0805_HandSoldering";1;"10k";;;
8;"C1,C2,C3,C6,C7";"C_0805_HandSoldering";5;"0.1u";;;
9;"C4,C5";"C_0805_HandSoldering";2;"22p";;;
10;"U1";"SOIC-16_3.9x9.9mm_Pitch1.27mm";1;"CH340G";;;
11;"Y1";"Crystal_SMD_HC49-SD";1;"12M";;;
12;"D1";"SLV6A-FKB";1;"LED_RGB";;;
13;"C8";"R_1206_HandSoldering";1;"100u";;;

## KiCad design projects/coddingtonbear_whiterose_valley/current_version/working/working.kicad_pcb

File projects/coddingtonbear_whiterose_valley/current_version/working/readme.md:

# whiterose
 
## summary 
* id: coddingtonbear_whiterose_valley
* user: coddingtonbear
* name: whiterose
* board: valley
* repo: https://github.com/coddingtonbear/whiterose
* src_file_repo_kicad_pcb: hardware/valley.kicad_pcb
* src_file_repo_kicad_pcb_link: https://github.com/coddingtonbear/whiterose/tree/master/hardware/valley.kicad_pcb

* src_file_repo_sch: hardware/valley.sch
* src_file_repo_sch_link: https://github.com/coddingtonbear/whiterose/tree/master/hardware/valley.sch
* full details link: https://github.com/oomlout/oomlout_oomp_project_bot_v_2/tree/main/projects/coddingtonbear_whiterose_valley/current_version/working

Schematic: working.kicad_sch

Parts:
C1, C2: 22p; 0805_Milling
C3: 0.1u; 0805_Milling
C12: 1000u; CAP-SMD-SIZE-F
D1: LED_RGB; SLV6A-FKB-MILLING
P2: USB_OTG; UJ2-MIBH-4-SMT
P4: CONN_01X16; Pin_Header_Straight_1x16_Pitch2.54mm
R1, R4: 10; 0805_Milling
R3, R7: 10k; 0805_Milling
R5: 150; 0805_Milling
U1: CH341A; SOIC-28W_7.5x17.9mm_Pitch1.27mm
U2: AP111733; SOT-223
U3: ESP32-WROOM
Y1: 12M; Crystal_SMD_HC49-SD_HandSoldering

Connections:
+3V3: C3.1, C12.1, P4.2, P4.15, R3.2, R7.1, U1.9, U1.28, U2.2, U2.4, U3.2
+5V: P2.1 (VBUS), U2.3
A0: P4.10, U3.11
CS_SD: P4.3, U3.26
CS_TFT: P4.7, U3.9
DTR: R7.2, U1.20, U3.25
GND: C1.1, C2.1, C3.2, C12.2, D1.1, D1.2, D1.3, P2.5 (GND), P2.6 (shield), P4.1, P4.16, U1.12, U1.27, U2.1, U3.1, U3.15, U3.38, U3.39
LED_BLUE: R1.2, U3.31
LED_GREEN: R4.2, U3.30
LED_RED: R5.2, U3.29
MISO: P4.5, U3.14
MOSI: P4.4, P4.9, U3.16
unnamed: C1.2, U1.13, Y1.1
unnamed: C2.2, U1.14, Y1.2
unnamed: D1.4, R1.1
unnamed: D1.5, R4.1
unnamed: D1.6, R5.1
RESET_TFT: P4.11, U3.10
RTS: R3.1, U1.21, U3.3
RXD: U1.5, U3.34
SCK: P4.6, P4.8, U3.13
TXD: U1.6, U3.35
UD+: P2.3 (D+), U1.10
UD-: P2.2 (D-), U1.11
USB_CONNECTED: U1.1, U3.33
